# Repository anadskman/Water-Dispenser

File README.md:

# Water-Dispenser

A custom-built smart drink dispenser that mixes water and blackcurrant concentrate on demand using two independently controlled pumps. The system is powered by an ESP32 and features adjustable mixing ratios, WiFi connectivity, cooling support, and a custom PCB.

## Overview

The dispenser stores water and blackcurrant concentrate in separate containers. When the dispense button is pressed, both pumps activate and mix the liquids through a shared output nozzle. The ESP32 controls the pump speeds, allowing the drink strength to be adjusted either through a potentiometer or a future web interface.

## Features

- Adjustable water-to-syrup ratio
- ESP32-based control system
- Custom PCB designed in KiCad
- Food-safe tubing and liquid path
- Physical dispense button
- Potentiometer for ratio adjustment
- Status LED

---

## Hardware

### Fluid System

- 2L water bottle
- 2L blackcurrant concentrate bottle
- 2× 12V peristaltic pumps
- Food-safe silicone tubing
- Barbed Y-connector
- Single output nozzle

### Electronics

- ESP32-WROOM
- 12V DC barrel jack
- LM2596 buck converter
- 3.3V regulator
- 2× Logic-level MOSFETs
- 2× Flyback diodes
- 2× 100Ω gate resistors
- 2× 10kΩ pull-down resistors
- 10kΩ potentiometer
- Pushbutton
- Status LED
- 220Ω LED resistor
- Decoupling and smoothing capacitors

---

## Electronics Design

The schematic is centered around an ESP32-WROOM module.

Power enters through a 12V barrel jack and is split into two sections. The pumps run directly from the 12V rail, while an LM2596 buck converter steps the voltage down before a 3.3V regulator supplies power to the ESP32.

Each pump is controlled by a dedicated MOSFET driver circuit. A 100Ω gate resistor is used between the ESP32 and MOSFET gate, while a 10kΩ pull-down resistor ensures the pumps remain off during boot. Flyback diodes protect the electronics from motor-induced voltage spikes.

A pushbutton is connected using the ESP32's internal pull-up resistor, while a 10k potentiometer provides live adjustment of the syrup ratio. A status LED indicates operating state.

All grounds are shared throughout the system, and capacitors are used for voltage smoothing and noise reduction.

---

## PCB Design

The PCB was designed in KiCad.

### Design Process

1. Created the schematic and assigned footprints.
2. Performed the initial PCB layout.
3. Routed all traces.
4. Ran DRC checks and fixed any issues.
5. Ensured nothing was placed inside the ESP32 keep-out zone.
6. Exported the PCB as a STEP file.
7. Imported the PCB into Fusion 360.

---

## Enclosure Design

The enclosure was designed around the PCB and bottle mounting system.

### Design Changes

- Moved the LED, potentiometer, and button to the opposite side for better usability and appearance.
- Added a cutout for the barrel jack.
- Flipped the PCB orientation after discovering the bottle mounts blocked access to the power connector.
- Designed a dedicated PCB housing.
- Created a removable rear panel.
- Added mounting points for both pumps.
- Designed bottle mounts that allow the dispenser assembly to sit above the bottles.
- Added a central passage for routing outlet tubing.
- Planned to reverse one pump orientation to simplify tube routing.

---

## Current Status

### Completed

- [x] Project planning
- [x] Schematic design
- [x] PCB design and routing
- [x] DRC validation
- [x] STEP export
- [x] Fusion 360 integration
- [x] Enclosure design
- [x] Pump mounts
- [x] Bottle mounting system
- [x] Rear access panel

---

## Bill of Materials (BOM)

| Item | Description | Qty | Price (€) | Total (€) |
|------|-------------|-----|-----------|-----------|
| DC Power Jack | Socket DC Connectors | 1 | 1.46 | 1.46 |
| DC 12V Dosing Pump | Peristaltic Pump | 2 | 6.38 | 6.38 |
| ESP32 Development Board | CH340C | 1 | 5.32 | 5.32 |
| LM2596 Chip | DC Converter | 1 | 0.82 | 0.82 |
| AMS1117-3.3 | 3.3V Regulator | 1 | 1.48 | 1.48 |
| 16V 100µF Electrolytic Capacitor | Capacitor | 1 | 1.94 | 1.94 |
| 100nF Ceramic Capacitor | Decoupling Capacitor | 1 | 2.72 | 2.72 |
| Food-Grade Silicone Tubing | 4mm ID × 5mm OD | 1 | 0.99 | 0.99 |
| 2-Pin Screw Terminals | 2P Terminal Block | 2 | 2.24 | 4.48 |
| IRLZ44N | Logic-Level N-Channel MOSFET | 1 | 3.04 | 3.04 |
| Flyback Diodes | 1N4007 | 1 | 1.72 | 1.72 |
| 100Ω Gate Resistors | Gate Resistors | 2 | Owned | Owned |
| 10kΩ Pull-Down Resistors | Pull-Down Resistors | 2 | Owned | Owned |
| Momentary Pushbutton | 6mm Tactile Switch | 1 | Owned | Owned |
| Potentiometer Bourns 3386P Vertical | 10kΩ | 1 | 2.16 | 2.16 |
| LED | Red | 1 | Owned | Owned |
| 220Ω Resistor | LED Current Limiting Resistor | 1 | Owned | Owned |
| PCB | Water Dispenser PCB (5 pcs) | 5 | 11.79 | 11.79 |

### Cost Summary

| Item | Cost (€) |
|--------|---------|
| Parts Total | 44.30 |
| Shipping | 6.44 |
| **Grand Total** | **50.74** |

---

## Project Goals

The aim of this project is to create a compact, professional-looking drink dispenser that can accurately mix and dispense flavoured drinks while serving as a complete electronics, PCB design, firmware, and mechanical CAD project.

## Gallery

### PCB

### CAD

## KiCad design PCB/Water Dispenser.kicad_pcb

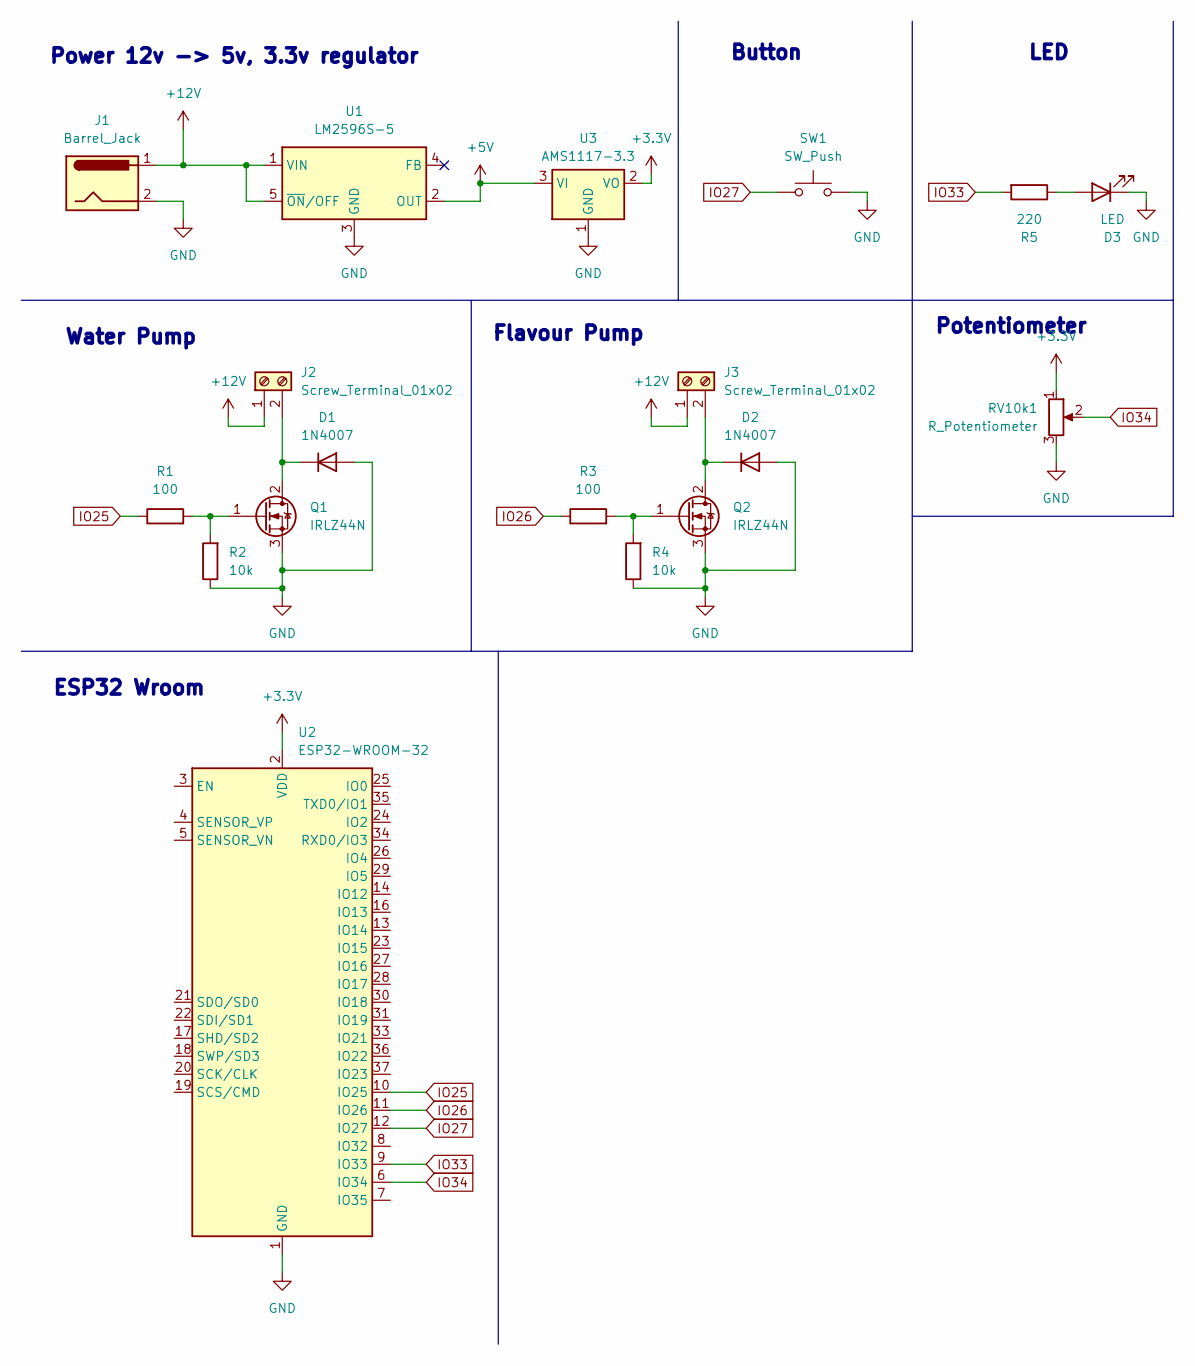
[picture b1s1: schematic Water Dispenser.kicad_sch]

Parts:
D1, D2: 1N4007; D_DO-41_SOD81_P10.16mm_Horizontal
D3: LED; LED_D5.0mm
J1: Barrel_Jack; BarrelJack_CUI_PJ-102AH_Horizontal
J2, J3: Screw_Terminal_01x02; TerminalBlock_Phoenix_MKDS-1,5-2-5.08_1x02_P5.08mm_Horizont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
Q1, Q2: IRLZ44N; TO-220-3_Vertical
R1, R3: 100; R_Axial_DIN0207_L6.3mm_D2.5mm_P5.08mm_Vertical
R2, R4: 10k; R_Axial_DIN0207_L6.3mm_D2.5mm_P5.08mm_Vertical
R5: 220; R_Axial_DIN0207_L6.3mm_D2.5mm_P5.08mm_Vertical
RV10k1: R_Potentiometer; Potentiometer_Bourns_3386P_Vertical
SW1: SW_Push; SW_PUSH_6mm_H4.3mm
U1: LM2596S-5; TO-263-5_TabPin3
U2: ESP32-WROOM-32
U3: AMS1117-3.3; SOT-223-3_TabPin2

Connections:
+3.3V: RV10k1.1, U2.2 (VDD), U3.2 (VO)
+5V: U1.2 (OUT), U3.3 (VI)
+12V: J1.1, J2.1, J3.1, U1.1 (VIN), U1.5 (~ON/OFF)
GND: D1.2 (A), D2.2 (A), D3.1 (K), J1.2, Q1.3 (S), Q2.3 (S), R2.1, R4.1, RV10k1.3, SW1.2, U1.3 (GND), U2.1 (GND), U2.15 (GND), U2.38 (GND), U2.39 (GND), U3.1 (GND)
IO25: R1.1, U2.10 (IO25)
IO26: R3.1, U2.11 (IO26)
IO27: SW1.1, U2.12 (IO27)
IO33: R5.2, U2.9 (IO33)
IO34: RV10k1.2, U2.6 (IO34)
unnamed: D1.1 (K), J2.2, Q1.2 (D)
unnamed: D2.1 (K), J3.2, Q2.2 (D)
unnamed: D3.2 (A), R5.1
unnamed: Q1.1 (G), R1.2, R2.2
unnamed: Q2.1 (G), R3.2, R4.2

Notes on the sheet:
Flavour Pump
LED
Water Pump
Button
Potentiometer
ESP32 Wroom
Power 12v -> 5v, 3.3v regulator

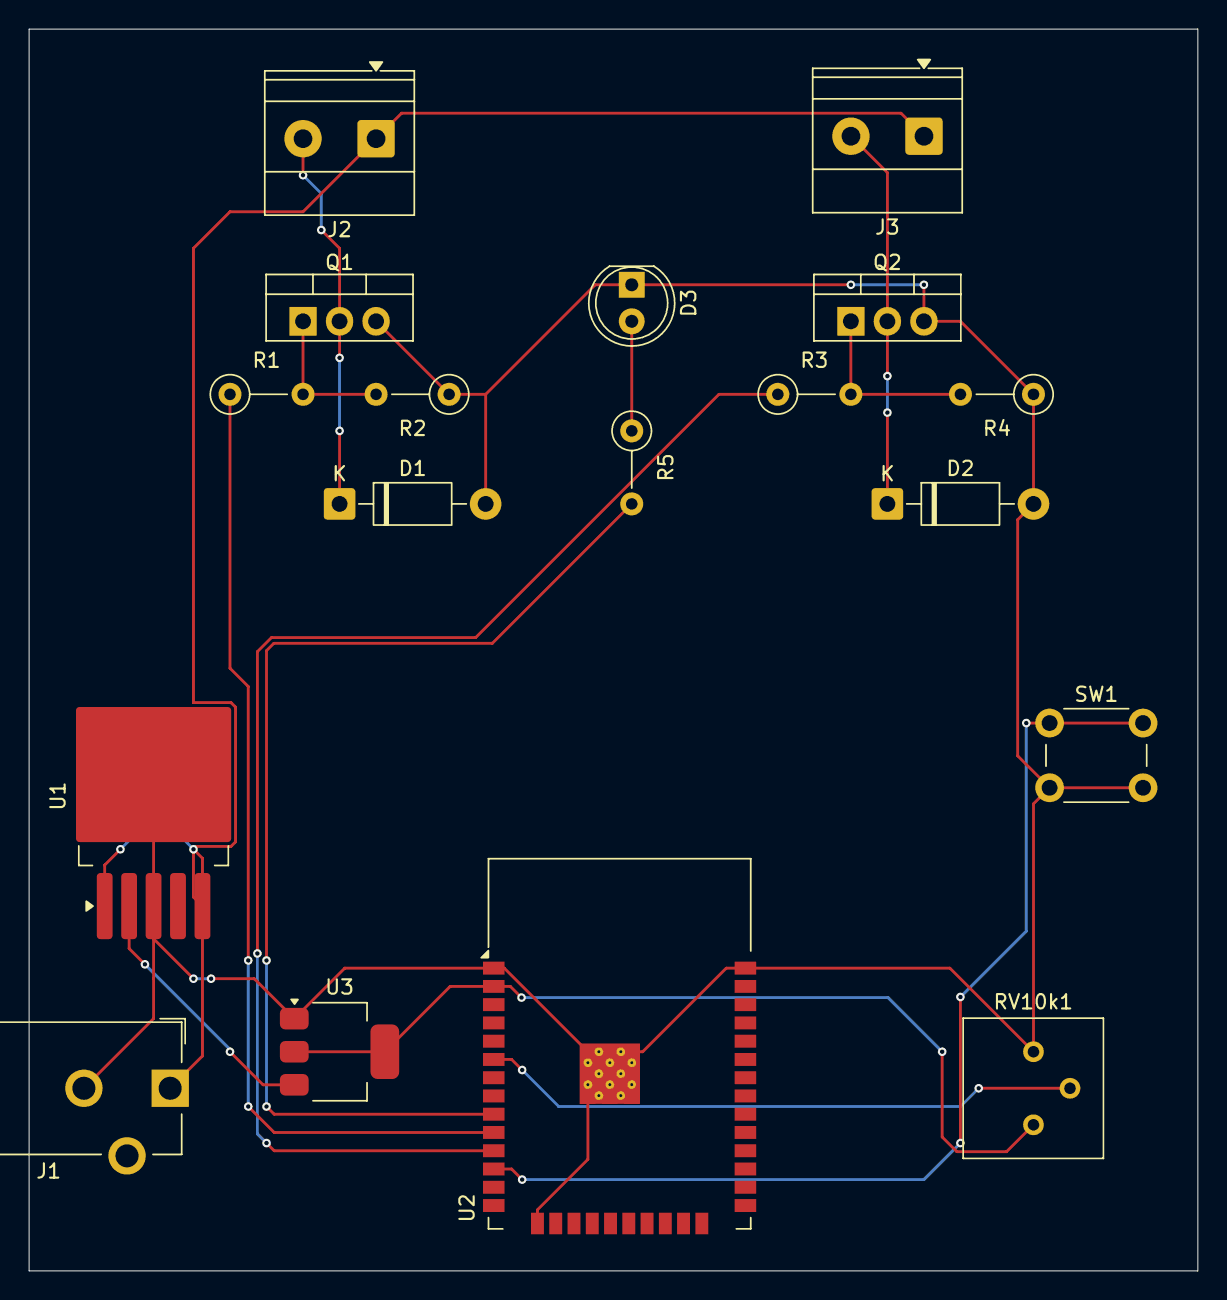
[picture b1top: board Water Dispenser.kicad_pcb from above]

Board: 2 copper layers, 81.3 x 86.4 mm, 18 parts (0 on the bottom side), 14 nets.

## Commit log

2026-05-31 Uploaded all files
2026-05-31 Update README.md to remove screenshot placeholders
    Removed placeholder text for screenshots in PCB and CAD sections.
2026-06-04 Update README with BOM and Cost Summary
    Added Bill of Materials (BOM) and Cost Summary sections to README.
2026-06-04 stl file
